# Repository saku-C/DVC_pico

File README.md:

# DVC-PICO v2 Controller & Analyzer

RP2040（Raspberry Pi Pico / Pico 2）をベースにした、多機能なDMX-512コントローラーおよびオシロスコープ・アナライザープロジェクトです。
ハードウェア（KiCad設計データ）とファームウェア（Arduinoスケッチ）が一体となって管理されています。

内部構造
https://qiita.com/kurumi18891/private/b40f511b77fc0b5f25af

操作マニュアル
https://qiita.com/kurumi18891/private/ef590465823563e47984

---

## 📂 フォルダ構成

```
DVC_pico2_1/ (リポジトリルート)
├── DVC_pico2_1.ino        # メインファームウェア (Arduinoスケッチ)
├── .gitignore             # Git除外設定ファイル
├── README.md              # 本ドキュメント
├── antigra_DVCpico/       # 補助フォルダ
└── kicad_DVC_pico/        # ハードウェア設計データ
    └── DVC-picov2/        # KiCad v2 回路図・基板アートワーク
        ├── DVC-picov2.kicad_pcb # 基板レイアウト
        ├── DVC-picov2.kicad_pro # KiCad プロジェクトファイル
        ├── DVC-picov2.kicad_sch # 回路図
        └── ...
```

---

## ✨ 主な機能

1. **多彩な通信モード（6チャネル拡張）**
   * **Monitor Only**: 送受信データの監視
   * **Read DMX -> SD**: 受信したDMXデータをCSV形式でSDカードにリアルタイム録画
   * **Write DMX <- SD**: SDカードに記録されたCSVファイルを再生し、DMX信号を出力
   * **Read DMX -> USB**: DMXデータをUSBシリアル経由でPCに送信
   * **Write DMX <- USB**: USB経由で受信したコマンドに基づいてDMX信号を出力
   * **Manual Controller**: 7つの操作キーを使用した、手動でのDMXチャンネル出力制御
2. **5つの画面表示モード**
   * **Waveform Monitor**: DMX各チャネルの値を波形（オシロスコープスタイル）でビジュアル表示
   * **Table Monitor**: DMX 512チャネルの数値をグリッド状に一覧表示
   * **Dashboard**: システムの稼働ステータスや通信統計、診断結果をサマリー表示
   * **Fixture Inspector**: 灯体（フィクスチャ）のチャンネル定義と設定値の確認
   * **Multi-Light Monitor**: 10灯のインテリジェントライトの個別モニターおよびプロファイル調整
3. **対話型フィクスチャ（灯体）エディター**
   * 接続されたDMX機器のチャンネル数や各チャンネルの役割（Dimmer, Red, Green, Blue, Strobe等）を本体キーで自由に変更・カスタム可能
4. **永続データ保存（EEPROMエミュレーション）**
   * 設定したフィクスチャのプロファイルデータをRP2040の内蔵フラッシュメモリに自動で保存・復元

---

## 🛠️ ハードウェア仕様とピン配置

### 主要コンポーネント
* **MCU**: Raspberry Pi Pico / Pico 2 (RP2040 / RP2350)
* **ディスプレイ**: 1.8インチ ST7735 TFTカラー液晶 (160x128)
* **外部ストレージ**: MicroSDカードスロット（ソフトウェアSPI動作）
* **DMXインターフェース**: MAX485トランシーバー搭載

### ピン割り当て (RP2040)
* **TFT ディスプレイ**:
  * `CS`  -> GPIO 22
  * `RST` -> GPIO 21
  * `DC`  -> GPIO 20
  * `LED` -> GPIO 17
* **SDカード (SoftSPI)**:
  * `SCK`  -> GPIO 10
  * `MISO` -> GPIO 11
  * `MOSI` -> GPIO 12
  * `CS`   -> GPIO 13
* **DMX**:
  * `TX`    -> GPIO 0
  * `RX`    -> GPIO 1
  * `RE_DE` -> GPIO 2
* **操作ボタン (Active LOW)**:
  * `SETTING` -> GPIO 9
  * `UP`      -> GPIO 8
  * `DOWN`    -> GPIO 4
  * `LEFT`    -> GPIO 6
  * `RIGHT`   -> GPIO 7
  * `ENTER`   -> GPIO 5
  * `BACK`    -> GPIO 3

---

## ⚙️ 開発環境と依存ライブラリ

ファームウェアをコンパイルするには、Arduino IDEに以下のライブラリを追加してください：

* **Adafruit_GFX** (ディスプレイ描画用)
* **Adafruit_ST7735** (ST7735制御用)
* **SdFat** (SDカードの高速読み書き用)
* **Pico DMX (DmxInput / DmxOutput)** (Earle Philhower版コアのDMX送受信サポート)

*※ボードマネージャーは「Raspberry Pi Pico/RP2040 (Earle Philhower版)」の使用を想定しています。*

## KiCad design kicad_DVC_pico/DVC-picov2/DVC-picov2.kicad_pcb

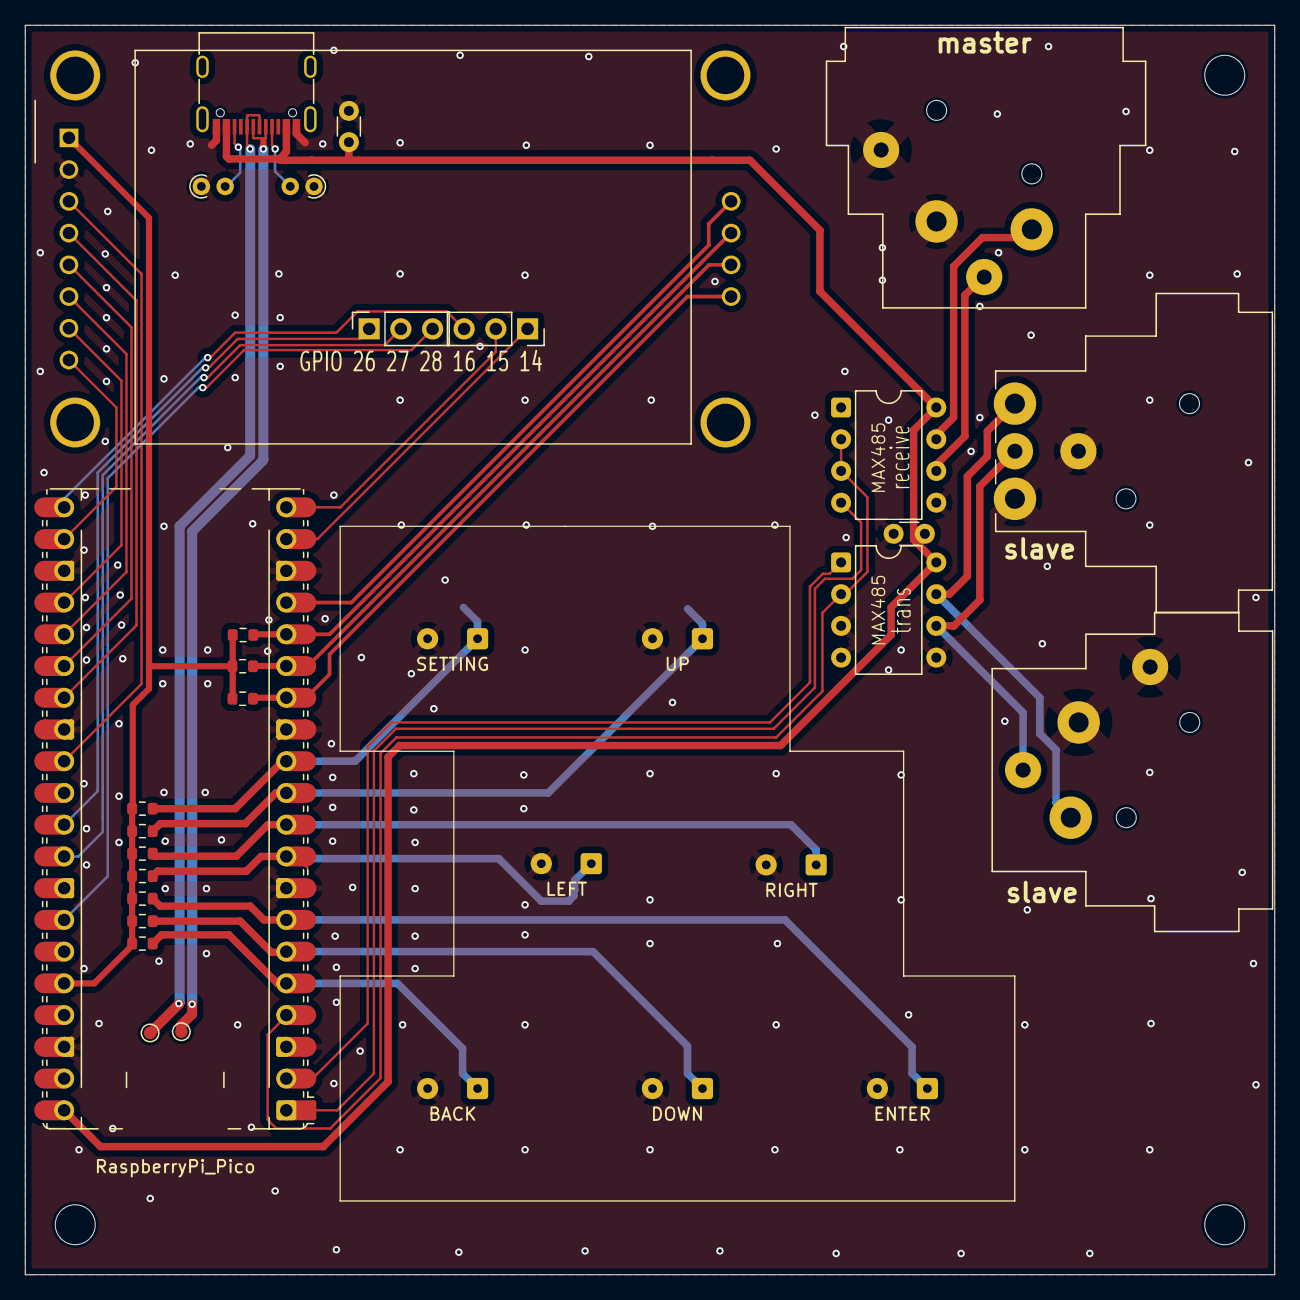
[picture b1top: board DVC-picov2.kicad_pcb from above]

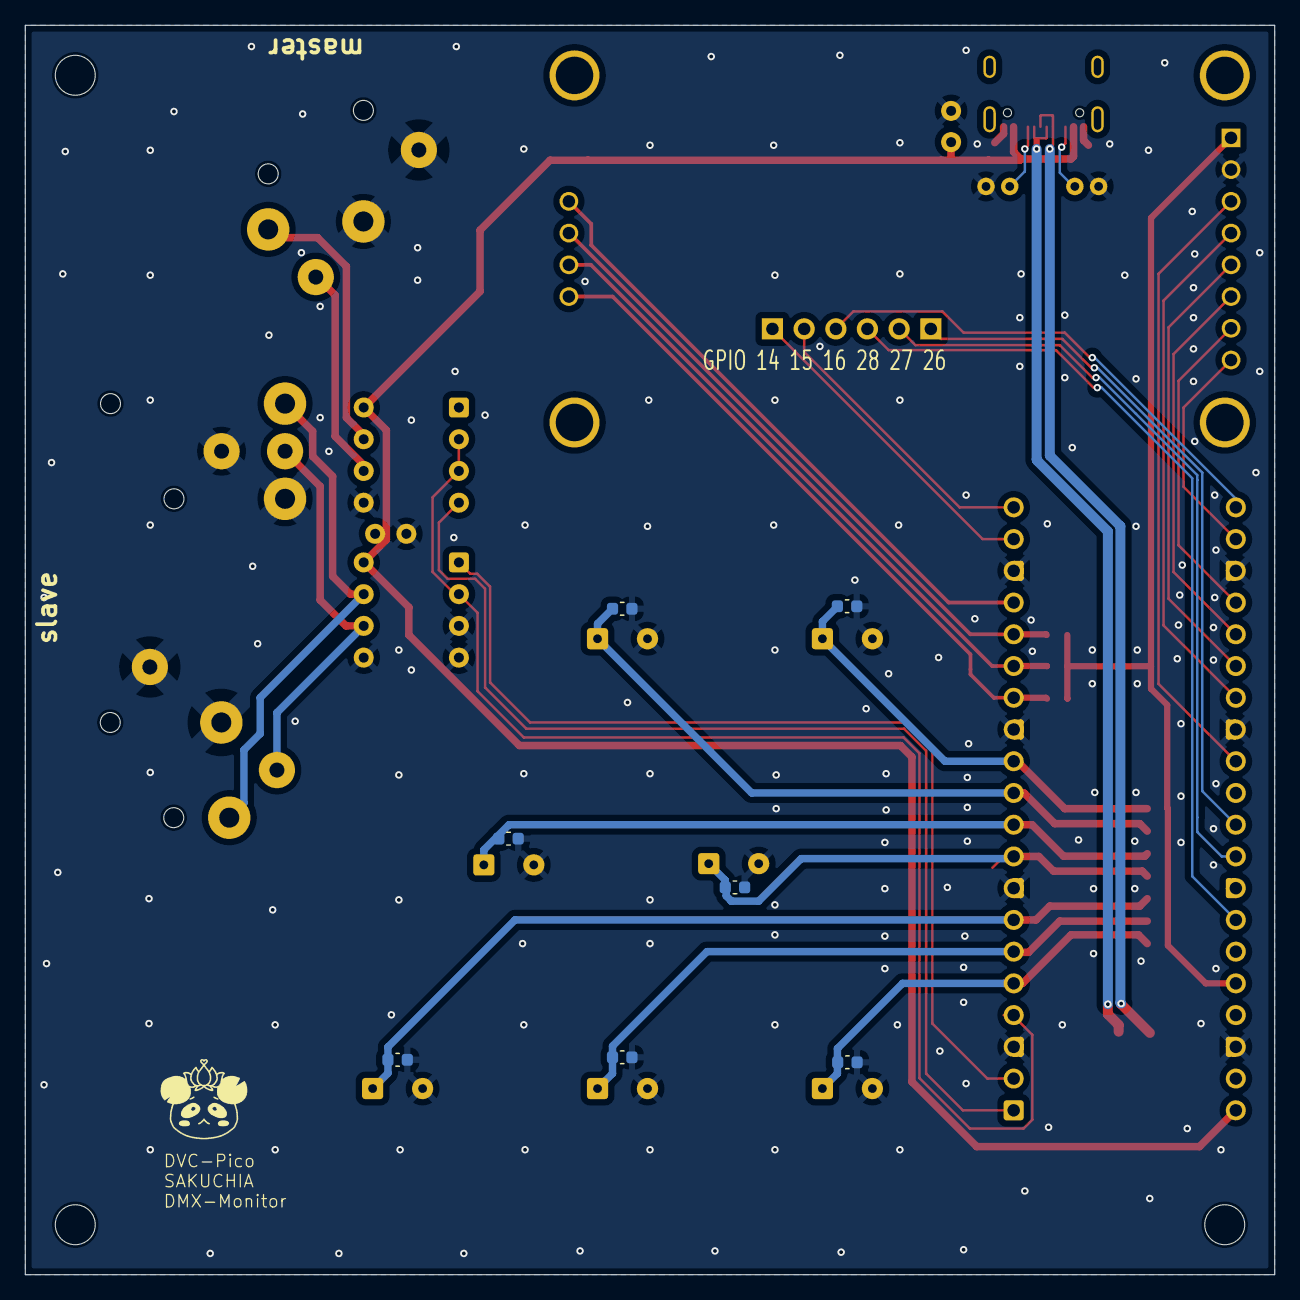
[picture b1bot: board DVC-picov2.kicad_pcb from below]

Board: 2 copper layers, 100.0 x 100.0 mm, 41 parts (7 on the bottom side), 37 nets.

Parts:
A1: RaspberryPi_Pico; RaspberryPi_Pico_Common_Unspecified
BACK: SW_Push; SolderWire-0.15sqmm_1x02_P4mm_D0.5mm_OD1.5mm
C1, C2: C; C_Disc_D3.0mm_W1.6mm_P2.50mm
C3, C4, C5, C6, C7, C8, C9: C; C_0603_1608Metric
DOWN: SW_Push; SolderWire-0.15sqmm_1x02_P4mm_D0.5mm_OD1.5mm
ENTER: SW_Push; SolderWire-0.15sqmm_1x02_P4mm_D0.5mm_OD1.5mm
H2, H3, H4: MountingHole; MountingHole_3.2mm_M3
J1: USB_C_Receptacle_USB2.0_16P; USB_C_Receptacle_G-Switch_GT-USB-7010ASV
J2, J3: XLR3_Ground; Jack_XLR_Neutrik_NC3FAH2-0_Horizontal
J4: XLR3_Ground; Jack_XLR_Neutrik_NC3MAH_Horizontal
J5, J6: Conn_01x03_Pin; PinSocket_1x03_P2.54mm_Vertical
LEFT: SW_Push; SolderWire-0.15sqmm_1x02_P4mm_D0.5mm_OD1.5mm
R1, R2: 5.1k; R_Axial_DIN0204_L3.6mm_D1.6mm_P1.90mm_Vertical
R3, R4, R5, R6, R7, R8, R9, R10, R11, R12: R; R_0603_1608Metric
RIGHT: SW_Push; SolderWire-0.15sqmm_1x02_P4mm_D0.5mm_OD1.5mm
SETTING: SW_Push; SolderWire-0.15sqmm_1x02_P4mm_D0.5mm_OD1.5mm
U1, U2: MAX485E; DIP-8_W7.62mm
U3: 1.8_TFT_SPI_128*160; 1.8_TFT_SPI_128_160_footprint
UP: SW_Push; SolderWire-0.15sqmm_1x02_P4mm_D0.5mm_OD1.5mm

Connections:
+3.3V: A1.36 (3V3), R3.1, R4.1, R5.1, R6.1, R7.1, R8.1, R9.1, R10.1, R11.1, R12.1, U3.1 (VCC)
A0: A1.26 (GPIO20), U3.5 (D/~C)
BTN_BACK: A1.5 (GPIO3), BACK.1, C3.1, R9.2
BTN_DOWN: A1.6 (GPIO4), C7.1, DOWN.1, R5.2
BTN_ENTER: A1.7 (GPIO5), C4.1, ENTER.1, R8.2
BTN_LEFT: A1.9 (GPIO6), C6.1, LEFT.1, R6.2
BTN_RIGHT: A1.10 (GPIO7), C5.1, R7.2, RIGHT.1
BTN_SETTING: A1.12 (GPIO9), C9.1, R3.2, SETTING.1
BTN_UP: A1.11 (GPIO8), C8.1, R4.2, UP.1
D+: J1.A6 (D+), J1.B6 (D+)
D-: J1.A7 (D-), J1.B7 (D-)
DMX_RX: A1.2 (GPIO1), U1.1 (RO)
DMX_TX: A1.1 (GPIO0), U2.4 (DI)
DMX_master_D+: J3.3, U2.6 (A)
DMX_master_D-: J3.2, U2.7 (B)
DMX_slave_D+: J2.3, J4.3, U1.6 (A)
DMX_slave_D-: J2.2, J4.2, U1.7 (B)
GND: A1.3 (GND), A1.8 (GND), A1.13 (GND), A1.18 (GND), A1.23 (GND), A1.28 (GND), A1.38 (GND), BACK.2, C1.2, C2.2, C3.2, C4.2, C5.2, C6.2, C7.2, C8.2, C9.2, DOWN.2, ENTER.2, J1.A1 (GND), J1.A12 (GND), J1.B1 (GND), J1.B12 (GND), J2.1, J2.G, J3.1, J3.G, J4.1, J4.G, LEFT.2, R1.1, R2.1, RIGHT.2, SETTING.2, U1.3 (DE), U1.4 (DI), U1.5 (GND), U2.5 (GND), U3.2 (GND), UP.2
GPIO14: A1.19 (GPIO14), J5.1
GPIO15: A1.20 (GPIO15), J5.2
GPIO16: A1.21 (GPIO16), J5.3
GPIO26: A1.31 (GPIO26_ADC0), J6.1
GPIO27: A1.32 (GPIO27_ADC1), J6.2
GPIO28: A1.34 (GPIO28_ADC2), J6.3
LED: A1.22 (GPIO17), U3.8 (LED)
MAX485_RE_DE: A1.4 (GPIO2), U1.2 (~RE), U2.2 (~RE), U2.3 (DE)
unnamed: J1.A5 (CC1), R2.2
unnamed: J1.B5 (CC2), R1.2
RESET: A1.27 (GPIO21), U3.4 (RESET)
SCK: A1.24 (GPIO18), U3.7 (SCK)
SDA: A1.25 (GPIO19), U3.6 (MOSI)
SD_CS: A1.17 (GPIO13), U3.9 (SD_CS)
SD_MISO: A1.15 (GPIO11), R11.2, U3.11 (SD_MISO)
SD_MOSI: A1.16 (GPIO12), R12.2, U3.10 (SD_MOSI)
SD_SCK: A1.14 (GPIO10), R10.2, U3.12 (SD_SCK)
VBUS: A1.40 (VBUS), C1.1, C2.1, J1.A4 (VBUS), J1.A9 (VBUS), J1.B4 (VBUS), J1.B9 (VBUS), U1.8 (VCC), U2.8 (VCC)
^cs: A1.29 (GPIO22), U3.3 (~CS)

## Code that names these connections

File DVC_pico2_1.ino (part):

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  #define TFT_DC    20
  #define TFT_LED   17

  #define SD_SCK  10
  #define SD_MISO 11 // 回路図実態に合わせてアサイン
  #define SD_MOSI 12 // 回路図実態に合わせてアサイン
  #define SD_CS   13

// --- ソフトウェアSPIオブジェクトの定義 ---
SoftSpiDriver<SD_MISO, SD_MOSI, SD_SCK> softSpi;
SdFat SD;

  #define MAX485_RE_DE  2

  #define DMX_TX_PIN 0
  #define DMX_RX_PIN 1

  #define BTN_SETTING 9
  #define BTN_UP      8
  #define BTN_DOWN    4
  #define BTN_LEFT    6
  #define BTN_RIGHT   7
  #define BTN_ENTER   5
  #define BTN_BACK    3

  #define SWITCH_QUANTITY 7
//
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    Serial.println("SD initialization done (Software SPI).");
  }

  dmxOut.begin(DMX_TX_PIN);
  dmxIn.begin(DMX_RX_PIN, 1, 512);
  dmxIn.read_async((uint8_t*)dmxData);

  pinMode(MAX485_RE_DE, OUTPUT);
  digitalWrite(MAX485_RE_DE, LOW);

  pinMode(BTN_UP, INPUT_PULLUP);
  pinMode(BTN_DOWN, INPUT_PULLUP);
  pinMode(BTN_LEFT, INPUT_PULLUP);
  pinMode(BTN_RIGHT, INPUT_PULLUP);
  pinMode(BTN_ENTER, INPUT_PULLUP);
  pinMode(BTN_BACK, INPUT_PULLUP);
  pinMode(BTN_SETTING, INPUT_PULLUP);

  // --- デモ10ライトセットの初期配置 & ロード ---
  if (!loadFixturesFromFlash()) {
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
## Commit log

2026-05-25 Initial commit: Add DVC-PICO v2 firmware and hardware
2026-05-25 Update README with additional project links
    Added links to related projects in the README.
